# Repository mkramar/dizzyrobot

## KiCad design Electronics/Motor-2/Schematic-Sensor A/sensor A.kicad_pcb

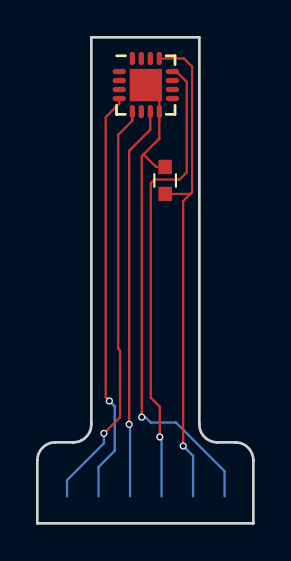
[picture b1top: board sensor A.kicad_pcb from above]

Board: 2 copper layers, 12.0 x 27.0 mm, 3 parts (1 on the bottom side), 6 nets.

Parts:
C1: C_Small; C_0603
J1: CONN_01X06; SPI_CONN
U1: MA700; QFN-16-1EP_3x3mm_Pitch0.5mm

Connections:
+3V3: C1.2, J1.5, U1.13
CS: J1.1, U1.5
Earth: C1.1, J1.6, U1.8, U1.17
MISO: J1.3, U1.7
MOSI: J1.2, U1.4
SCLK: J1.4, U1.12

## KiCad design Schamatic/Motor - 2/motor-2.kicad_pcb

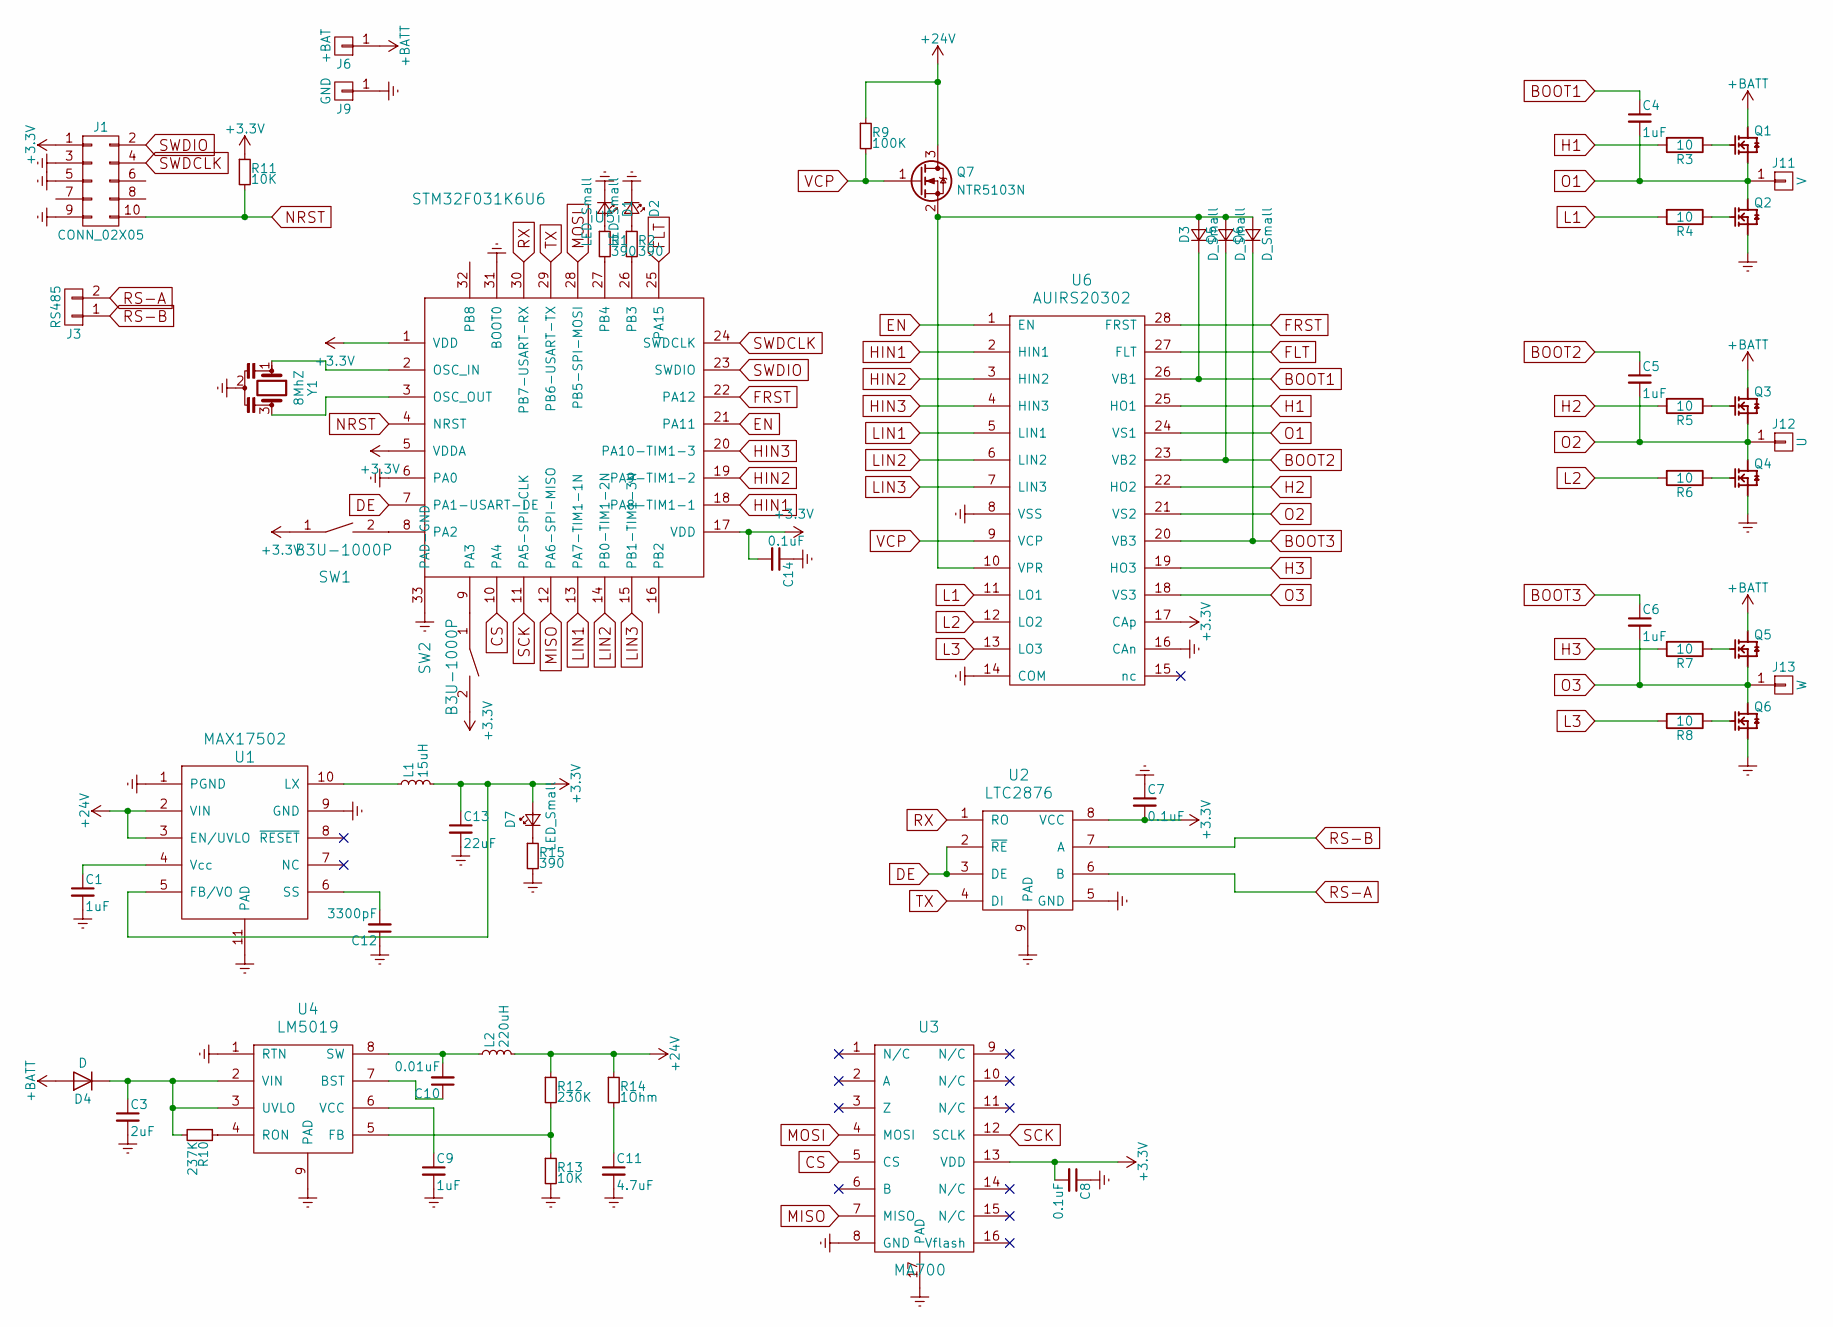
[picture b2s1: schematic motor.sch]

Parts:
C1, C4, C5, C6, C9: 1uF; C_0603
C3: 2uF; C_1206
C7, C8, C14: 0.1uF; C_0603
C10: 0.01uF; C_0603
C11: 4.7uF; C_1206
C12: 3300pF; C_0603
C13: 22uF; C_0805
D1, D2, D7: LED_Small; LED_0603
D3, D5, D6: D_Small; D_SOD-323F
D4: D; D_SOD-323F
J1: CONN_02X05; Pin_Header_Straight_2x05_Pitch1.27mm_SMD
J3: RS485; Pin_Header_Straight_1x02_Pitch2.54mm
J6: +BAT; Pin_Header_Straight_1x01_Pitch2.54mm
J9: GND; Pin_Header_Straight_1x01_Pitch2.54mm
J11: V; Pin_Header_Straight_1x01_Pitch2.54mm
J12: U; Pin_Header_Straight_1x01_Pitch2.54mm
J13: W; Pin_Header_Straight_1x01_Pitch2.54mm
L1: 15uH; L_1210
L2: 220uH; L_1210
Q1, Q3, Q5: PSMN3R3-40YS
Q2, Q4, Q6: PSMN3R3-40YS; PSMN3R3-40YS-vias
Q7: NTR5103N
R1, R2, R15: 390; R_0603
R3, R4, R5, R6, R7, R8: 10; R_0603
R9: 100K; R_0603
R10: 237K; R_0603
R11, R13: 10K; C_0603
R12: 230K; C_0603
R14: 1Ohm; C_0603
SW1, SW2: B3U-1000P; R_1206
U1: MAX17502; DFN-10-1EP_2x3mm_Pitch0.5mm
U2: LTC2876
U3: MA700; QFN-16-1EP_3x3mm_Pitch0.5mm
U4: LM5019; DFN-8-1EP_4x4mm_Pitch0.8mm
U5: STM32F031K6U6; UFQFPN32-small-pad
U6: AUIRS20302; SOIC-28W_7.5x18.7mm_Pitch1.27mm
Y1: 8MhZ; Oscillator

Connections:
+3V3: C7.2, C8.2, C13.1, C14.2, D7.2 (A), J1.1, L1.2, R11.1, SW1.1, SW2.2, U1.5 (FB/VO), U2.8 (VCC), U3.13 (VDD), U5.1 (VDD), U5.5 (VDDA), U5.17 (VDD), U6.17 (CAp)
+24V: L2.2, Q7.3 (D), R9.1, R12.1, R14.1, U1.2 (VIN), U1.3 (EN/UVLO)
+BATT: D4.2 (A), J6.1, Q1.5678 (D), Q3.5678 (D), Q5.5678 (D)
BOOT1: C4.1, D3.1 (K), U6.26 (VB1)
BOOT2: C5.1, D5.1 (K), U6.23 (VB2)
BOOT3: C6.1, D6.1 (K), U6.20 (VB3)
CS: U3.5 (CS), U5.10 (PA4)
DE: U2.2 (~RE), U2.3 (DE), U5.7 (PA1-USART-DE)
EN: U5.21 (PA11), U6.1 (EN)
Earth: C1.2, C3.2, C7.1, C8.1, C9.2, C11.2, C12.1, C13.2, C14.1, D1.1 (K), D2.1 (K), J1.3, J1.5, J1.9, J9.1, Q2.1 (S), Q2.2 (S), Q2.3 (S), Q4.1 (S), Q4.2 (S), Q4.3 (S), Q6.1 (S), Q6.2 (S), Q6.3 (S), R13.2, R15.2, U1.1 (PGND), U1.9 (GND), U1.11 (PAD), U2.5 (GND), U2.9 (PAD), U3.8 (GND), U3.17 (PAD), U4.1 (RTN), U4.9 (PAD), U5.6 (PA0), U5.31 (BOOT0), U5.33 (PAD-GND), U6.8 (VSS), U6.14 (COM), U6.16 (CAn), Y1.2; also elsewhere on the board
FLT: U5.25 (PA15), U6.27 (FLT)
FRST: U5.22 (PA12), U6.28 (FRST)
H1: R3.2, U6.25 (HO1)
H2: R5.2, U6.22 (HO2)
H3: R7.2, U6.19 (HO3)
HIN1: U5.18 (PA8-TIM1-1), U6.2 (HIN1)
HIN2: U5.19 (PA9-TIM1-2), U6.3 (HIN2)
HIN3: U5.20 (PA10-TIM1-3), U6.4 (HIN3)
L1: R4.2, U6.11 (LO1)
L2: R6.2, U6.12 (LO2)
L3: R8.2, U6.13 (LO3)
LIN1: U5.13 (PA7-TIM1-1N), U6.5 (LIN1)
LIN2: U5.14 (PB0-TIM1-2N), U6.6 (LIN2)
LIN3: U5.15 (PB1-TIM1-3N), U6.7 (LIN3)
MISO: U3.7 (MISO), U5.12 (PA6-SPI-MISO)
MOSI: U3.4 (MOSI), U5.28 (PB5-SPI-MOSI)
NRST: J1.10, R11.2, U5.4 (NRST)
unnamed: C1.1, U1.4 (Vcc)
unnamed: C3.1, D4.1 (K), R10.2, U4.2 (VIN), U4.3 (UVLO)
unnamed: C9.1, U4.6 (VCC)
unnamed: C10.1, U4.7 (BST)
unnamed: C10.2, L2.1, U4.8 (SW)
unnamed: C11.1, R14.2
unnamed: C12.2, U1.6 (SS)
unnamed: D1.2 (A), R1.1
unnamed: D2.2 (A), R2.1
unnamed: D3.2 (A), D5.2 (A), D6.2 (A), Q7.2 (S), U6.10 (VPR)
unnamed: D7.1 (K), R15.1
unnamed: L1.1, U1.10 (LX)
unnamed: Q1.4 (G), R3.1
unnamed: Q2.4 (G), R4.1
unnamed: Q3.4 (G), R5.1
unnamed: Q4.4 (G), R6.1
unnamed: Q5.4 (G), R7.1
unnamed: Q6.4 (G), R8.1
unnamed: R1.2, U5.27 (PB4)
unnamed: R2.2, U5.26 (PB3)
unnamed: R10.1, U4.4 (RON)
unnamed: R12.2, R13.1, U4.5 (FB)
unnamed: SW1.2, U5.8 (PA2)
unnamed: SW2.1, U5.9 (PA3)
unnamed: U5.2 (OSC_IN), Y1.1
unnamed: U5.3 (OSC_OUT), Y1.3
O1: C4.2, J11.1, Q1.1 (S), Q1.2 (S), Q1.3 (S), Q2.5678 (D), U6.24 (VS1)
O2: C5.2, J12.1, Q3.1 (S), Q3.2 (S), Q3.3 (S), Q4.5678 (D), U6.21 (VS2)
O3: C6.2, J13.1, Q5.1 (S), Q5.2 (S), Q5.3 (S), Q6.5678 (D), U6.18 (VS3)
RS-A: J3.2, U2.6 (B)
RS-B: J3.1, U2.7 (A)
RX: U2.1 (RO), U5.30 (PB7-USART-RX)
SCK: U3.12 (SCLK), U5.11 (PA5-SPI-CLK)
SWDCLK: J1.4, U5.24 (SWDCLK)
SWDIO: J1.2, U5.23 (SWDIO)
TX: U2.4 (DI), U5.29 (PB6-USART-TX)
VCP: Q7.1 (G), R9.2, U6.9 (VCP)

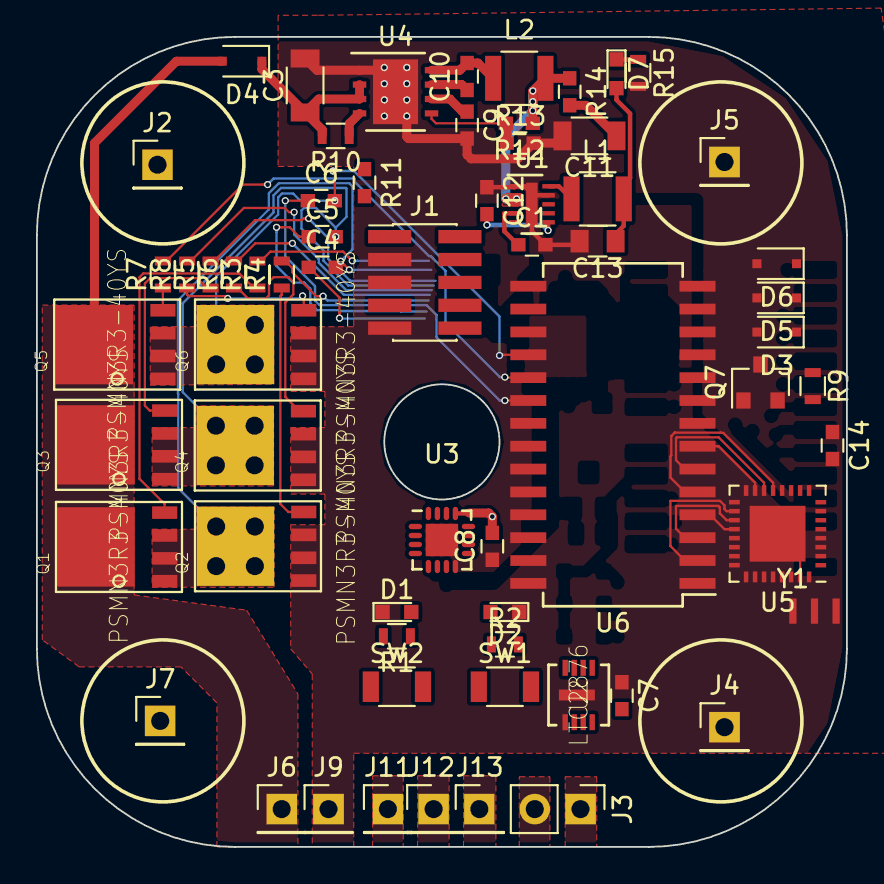
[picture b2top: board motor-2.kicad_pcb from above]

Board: 2 copper layers, 45.0 x 45.0 mm, 64 parts (0 on the bottom side), 64 nets.

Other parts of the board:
J2, J4, J5, J7: MOUNT; Pin_Header_Straight_1x01_Pitch2.54mm

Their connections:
Earth: J2.1, J4.1, J5.1, J7.1; also elsewhere on the board

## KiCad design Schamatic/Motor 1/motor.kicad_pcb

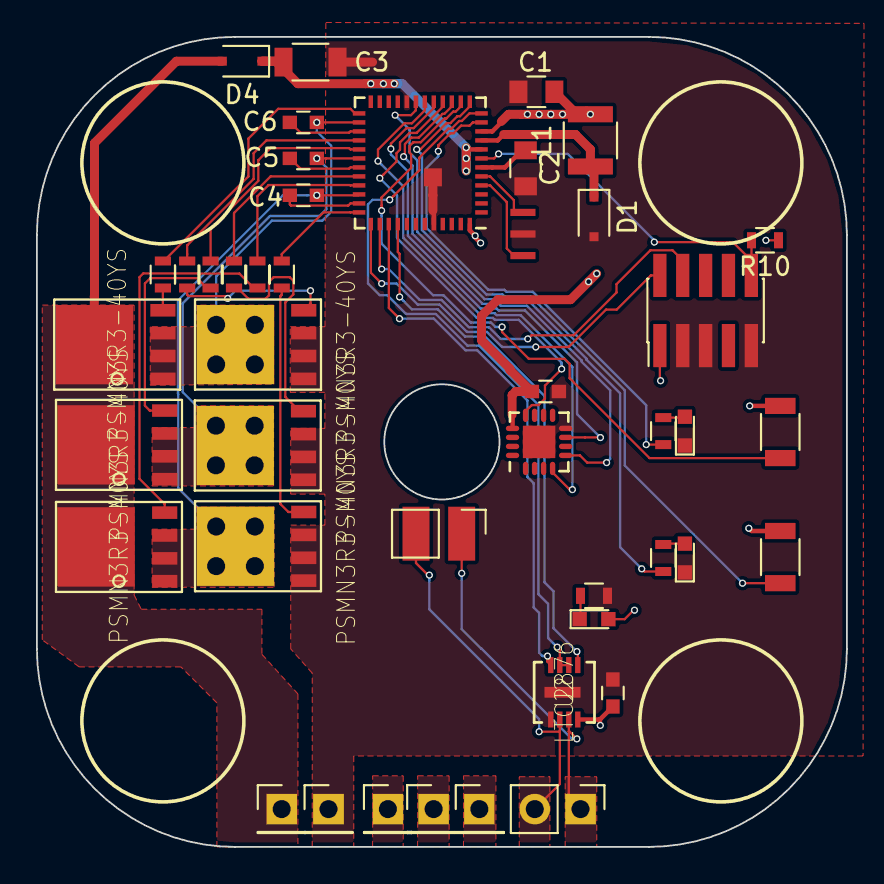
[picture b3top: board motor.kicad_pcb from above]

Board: 2 copper layers, 45.0 x 45.0 mm, 44 parts (0 on the bottom side), 45 nets.

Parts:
C1: 100uF; C_0805
C2: 22uF; C_0805
C3: 1uF; C_1206
C4, C5, C6, C7: 1uF; C_0603
C8: 0.1uF; C_0603
CALIB1: CALIB; R_1206
D1: CD0603-B0340R; D_SOD-323F
D2: CD0603-B0340R; LED_0603
D3: ID; LED_0603
D4: D; D_SOD-323F
D5: CALIB; LED_0603
ID1: ID; R_1206
J1: CONN_02X05; Pin_Header_Straight_2x05_Pitch1.27mm_SMD
J2, J3: RS485; Pin_Header_Straight_1x02_Pitch2.54mm
J6: 12; Pin_Header_Straight_1x01_Pitch2.54mm
J9: GND; Pin_Header_Straight_1x01_Pitch2.54mm
J11: V; Pin_Header_Straight_1x01_Pitch2.54mm
J12: U; Pin_Header_Straight_1x01_Pitch2.54mm
J13: W; Pin_Header_Straight_1x01_Pitch2.54mm
L1: 22uH; L_1210
Q1, Q3, Q5: PSMN3R3-40YS
Q2, Q4, Q6: PSMN3R3-40YS; PSMN3R3-40YS-vias
R1, R2, R9: 320; R_0603
R3, R4, R5, R6, R7, R8: 10; R_0603
R10: 10k; R_0603
U1: STSPIN32F0; STSPIN32-nopad
U2: LTC2876
U3: MA700; QFN-16-1EP_3x3mm_Pitch0.5mm
Y1: 8Mhz; Oscillator

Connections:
+3V3: C1.1, C7.2, C8.2, CALIB1.2, D2.2, ID1.2, J1.1, L1.2, R10.1, U1.10, U1.48, U2.8, U3.13
+12V: D4.2, J6.1, Q1.5678, Q3.5678, Q5.5678
BOOT1: C4.1, U1.35
BOOT2: C5.1, U1.31
BOOT3: C6.1, U1.27
CS: U1.15, U3.5
DE: U1.12, U2.2, U2.3
Earth: C1.2, C2.1, C3.2, C7.1, C8.1, D1.2, D3.1, D5.1, J1.3, J1.5, J1.9, J9.1, Q2.1, Q2.2, Q2.3, Q4.1, Q4.2, Q4.3, Q6.1, Q6.2, Q6.3, R9.2, U1.20, U1.44, U1.49, U2.5, U2.9, U3.8, U3.17, Y1.2
H1: R3.2, U1.33
H2: R5.2, U1.29
H3: R7.2, U1.25
L1: R4.2, U1.36
L2: R6.2, U1.32
L3: R8.2, U1.28
MISO: U1.17, U3.7
MOSI: U1.18, U3.4
NRST: J1.10, R10.2, U1.7
unnamed: C2.2, U1.6
unnamed: CALIB1.1, U1.14
unnamed: D1.1, L1.1, U1.9
unnamed: D2.1, R9.1
unnamed: D3.2, R1.2
unnamed: D5.2, R2.2
unnamed: ID1.1, U1.13
unnamed: Q1.4, R3.1
unnamed: Q2.4, R4.1
unnamed: Q3.4, R5.1
unnamed: Q4.4, R6.1
unnamed: Q5.4, R7.1
unnamed: Q6.4, R8.1
unnamed: R1.1, U1.19
unnamed: R2.1, U1.11
unnamed: U1.4, Y1.1
unnamed: U1.5, Y1.3
O1: C4.2, J11.1, Q1.1, Q1.2, Q1.3, Q2.5678, U1.34
O2: C5.2, J12.1, Q3.1, Q3.2, Q3.3, Q4.5678, U1.30
O3: C6.2, J13.1, Q5.1, Q5.2, Q5.3, Q6.5678, U1.26
RS-A: J2.2, J3.2, U2.6
RS-B: J2.1, J3.1, U2.7
RX: U1.40, U2.1
SCK: U1.16, U3.12
SWDCLK: J1.4, U1.38
SWDIO: J1.2, U1.37
TX: U1.39, U2.4
VM: C3.1, D4.1, U1.8
